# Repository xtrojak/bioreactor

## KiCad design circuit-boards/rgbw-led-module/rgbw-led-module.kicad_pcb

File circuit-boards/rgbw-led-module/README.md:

# RGBW LED module

This KiCad project describes a small PCB (12x20mm) that can accommodate a single high-power RGBW LED. Multiple such LEDs in parallel or series can be then used as light emitters in the bioreactor. 

<p align="center">&nbsp&nbsp</p>

Some notes and considerations about the design:
 
 - The module uses four resistors to normalise the current flow through each LED colour to 100mA at 4V. This means the modules can be chained together and powered from common 12V (three modules) or 20V (five modules) power sources.
 - Smaller voltages still mostly work, but the amount of light is proportionally smaller (2V seems to be nearing the lower limit of visible emission). You should use PWM for regulation, but 2V is useful for testing ;)
 - Each LED colour consumes approx. 0.2-0.3W (exact mcd numbers for light output are in the datasheet). The project is aimed at deployment of 30 LEDs, i.e. 6-9W of power *per* colour.
 - As such, note that at max current, the LED and the resistors can generate substantial amount of heat. It is not advised to run more than one colour at max power for longer periods of time (and even this should be avoided if possible).
 - The LED silkscreen has a highlighted corner where the mark on the LED should be oriented. (This is unfortunately missing on the first batch though!)
 - All SMD components have enlarged pads for manual soldering. Hot air reflow is easier at this size though.
 - The KiCad project uses a library of custom symbols and footprints for the LED. This should be imported automatickally (assuming you check out the whole project). However, in case of any unexpected errors, make sure you have both `symbols.lib` and `footprints.pretty` properly imported.
 - Note that at the moment, there isn't any spacing between the copper layer and the solder mask (It is customary to make the "holes" in the solder mask slightly larger than the pads). This is mainly because with the tolerances commonly used during manufacturing (min. 0.2mm width for any solder mask area), the LED pads would connect to a continuous area with no mask. As a result, the pads may be a bit smaller than specified, but it does not appear to be a problem during assembly, so leave this setting as is. Or make very very sure that the mask looks ok in the gerber files before you send them for production.

Some notes about possible future revisions:

 - Use a connector that does not require through-holes (Maybe just an SMD header? Or use glue to secure cables in place so that they won't break when soldered directly to the board).
 - Make space at the back of the LED for a small heatsink (up to 12x12mm). For example [this one](https://cz.mouser.com/ProductDetail/CUI-Devices/HSB02-101007) -- aliexpress seems to also have cheaper ones, but not by much.

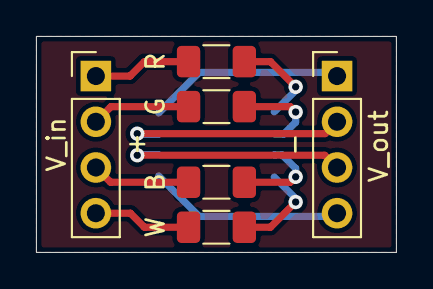
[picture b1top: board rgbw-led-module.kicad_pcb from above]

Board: 2 copper layers, 20.0 x 12.0 mm, 7 parts (1 on the bottom side), 12 nets.

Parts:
B: 9.09; R_1206_3216Metric_Pad1.30x1.75mm_HandSolder
G: 10; R_1206_3216Metric_Pad1.30x1.75mm_HandSolder
R: 19.1; R_1206_3216Metric_Pad1.30x1.75mm_HandSolder
RGBW_LED: GW+J9LHS1.4M_EN; RGBW_LED_GW_J9LHS1.4M_HandSolder
V_in: Pin Header; PinHeader_1x04_P2.54mm_Vertical
V_out: Pin Header; PinHeader_1x04_P2.54mm_Vertical
W: 10; R_1206_3216Metric_Pad1.30x1.75mm_HandSolder

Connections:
unnamed: R.2, RGBW_LED.1
unnamed: G.2, RGBW_LED.2
unnamed: B.2, RGBW_LED.3
unnamed: RGBW_LED.4, W.2
unnamed: RGBW_LED.5, V_out.4
unnamed: RGBW_LED.6, V_out.3
unnamed: RGBW_LED.7, V_out.2
unnamed: RGBW_LED.8, V_out.1
unnamed: B.1, V_in.3
unnamed: G.1, V_in.2
unnamed: R.1, V_in.1
unnamed: V_in.4, W.1

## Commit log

2021-10-27 Added basic bowl
2021-10-27 Added bowl in stl
2021-11-03 Smaller version (with 70mm radius) of the bowl
2021-11-04 Initial design of the mixing mechanism bearing.
2021-11-04 Separated bowl parts to individual files
2021-11-05 Updated version of bowl with correct dimensions and fine-tuned gap for the o-ring
2021-11-11 Add resources that describe the HiFive1-RevB board, including a small blinking LED example.
2021-11-11 Documentation and example code for the HTU21D sensor.
2021-11-11 Correct checksum implementation and a usable README file.
2021-11-13 Added Python example for htu21d I2C sensor
2021-11-17 Added example codes and specs for GA12-N20-motor, IRF520-MOSFET, PCA9685, and peristaltic pump
2021-11-17 Add cog for the mixing motor
2021-11-20 Add some basics to gitignore
2021-11-20 Update ga12-n20 motor readme.
2021-11-20 Update irf520 readme.
2021-11-21 Updated read-me and materials for the PCA9685 PWM controller.
2021-11-21 Normalize folder names.
2021-11-21 Update pump read-me.
2021-11-22 Add KiCAD project with a preliminary version of the PCB and schematics.
2021-11-26 Better PCB design.
2021-11-27 New version with thread directly created by the plugin
2021-11-27 Add information about available older components that we can reuse.
2021-11-28 Add a few additional components that could be useful.
2021-11-28 Add bullet points for better readability.
2021-11-29 Updated version of the board which actually goes through DRC checks.
2021-11-29 Remove mask clearances, because they are too loose for the LED pads.
2021-11-29 Add corner triangle placement indication to LED footprint.
2021-11-30 First version of pillars for led scaffold
2021-12-02 Smaller version of bowl
2021-12-03 Reduced gap for o-ring
2021-12-12 Add datasheet for the LEDs and some exported PDFs to the module.
2021-12-12 Add a short read-me to the project.
2022-03-20 Updated scaffold design.
2022-03-21 Cleaned-up scaffold design with production `.stl` files.
2022-03-21 Rename folder.
2022-03-31 Remove one of the redundant edge beam models.
2022-03-31 Add a readme.
2022-04-02 Main document describing the high-level specification of the front-end protocol.
2022-04-02 New version of bowl using screws
2022-04-02 Add some initial implementation of the hub server (only authentication and basic configuration).
2022-04-02 Add basic info about authentication.
2022-04-02 Rename file.
2022-04-02 Minor fixes in the authentication API.
2022-04-03 Rename `auth` to `api_auth`.
2022-04-03 Rotated orientation of screw, extended width
2022-04-03 Add API skeleton for obtaining info about the connected devices and modifying their status.
2022-04-10 Preliminary work on the low-level hub-device network communication protocol.
2022-05-25 Barebones control panel project.
2022-05-25 A version of the control panel with actually working login screen.
2022-06-15 Added MAX31865 converter with PT100 temperature sensor
2022-06-15 Added MCP3424 converter and HW390 sensor
2022-06-15 Add a few notes about board design and connecting probes with different number of leads.
2022-06-15 Add notes about schematics.
